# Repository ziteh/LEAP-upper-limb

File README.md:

# LEAP Upper Limb

> **Note**
> This study has ended and is no longer updated.

***LEAP-Up***, or "Lightweight Exoskeleton with Assistive Power, Upper Limb" is an upper limb powered exoskeleton based on the experience of develop [LEAP](https://github.com/ziteh/LEAP).  

- Firmware
  - [Master controller](/stm32/hi-level/): STM32Cube, STM32 HAL
  - [SIE joint code](/stm32/stm32_simple_foc/): PlatformIO, simpleFOC
  - [SFE joint code](/stm32/stm32_simple_foc/): PlatformIO, simopleFOC
  - [EFE joint code](/stm32/maxon_escon_pid_control/): PlatformIO, LibOpenCM3
- Hardware
  - PCB
    - [Master controller](/pcb/master-controller/)
    - [SIE/SFE joint](/pcb/motor-controller_simpleFOC/)
    - [EFE joint](/pcb/motor-controller_maxon/)
  - [Mechanical](/3d_model/)

# Part List

- MCU
  - STM32 NUCLEO-F446RE: Master controller and EFE joint
  - STM32 NUCLEO-L432KC: SIE and SFE joints
- Gear
  - SHD-25-100-2SH-SP: SIE joint
  - CSD-32-100-2A-GR: SFE joint
  - maxon GP 32 S: EFE joint
- Motor
  - T-Motor U8: SIE joint
  - T-Motor U10II: SFE joint
  - maxon EC-i30: EFE joint
- Motor Driver
  - ZONRI DRV8302: SIE and SFE joints
  - maxon ESCON 70/10: EFE joint
- Sensor
  - WACOH WEF-6A200-4-RCD: 6-Axis force sensor
  - ams-OSRAM AS5047P: Angle sensor/encoder
- Others
  - MAX490: RS-422 to UART

# Environment

- Ubuntu 20.04.3 'Focal Fossa' LTS (64-bit)
  - ROS 2 Foxy Fitzroy
- MATLAB R2020a
  - Robotics Toolbox for MATLAB `Ver. 10.4`
- STM32
  - PlatformIO IDE for VSCode `Ver. 3.4.4`
    - Core `Ver. 6.1.9`
    - Platform: ST STM32 `Ver. 15.6.0`
  - ~~Atollic TrueSTUDIO for STM32 `Ver. 9.3.0`~~
  - STM32Cube
    - MX: `Ver 6.7.0`
    - IDE: `Ver 1.12.0`
  - SimpleFOC: `Ver 2.2.3`
- Autodesk Inventor professional 2022

# Reference

- [SimpleFOC](https://simplefoc.com/)
- [stm32-examples](https://github.com/ziteh/stm32-examples)
  - [libopencm3](https://ziteh.github.io/series/%E7%B0%A1%E5%96%AE%E5%85%A5%E9%96%80-libopencm3-stm32-%E5%B5%8C%E5%85%A5%E5%BC%8F%E7%B3%BB%E7%B5%B1%E9%96%8B%E7%99%BC/)
- [libopencm3 Developer Documentation](https://libopencm3.org/docs/latest/html/index.html)

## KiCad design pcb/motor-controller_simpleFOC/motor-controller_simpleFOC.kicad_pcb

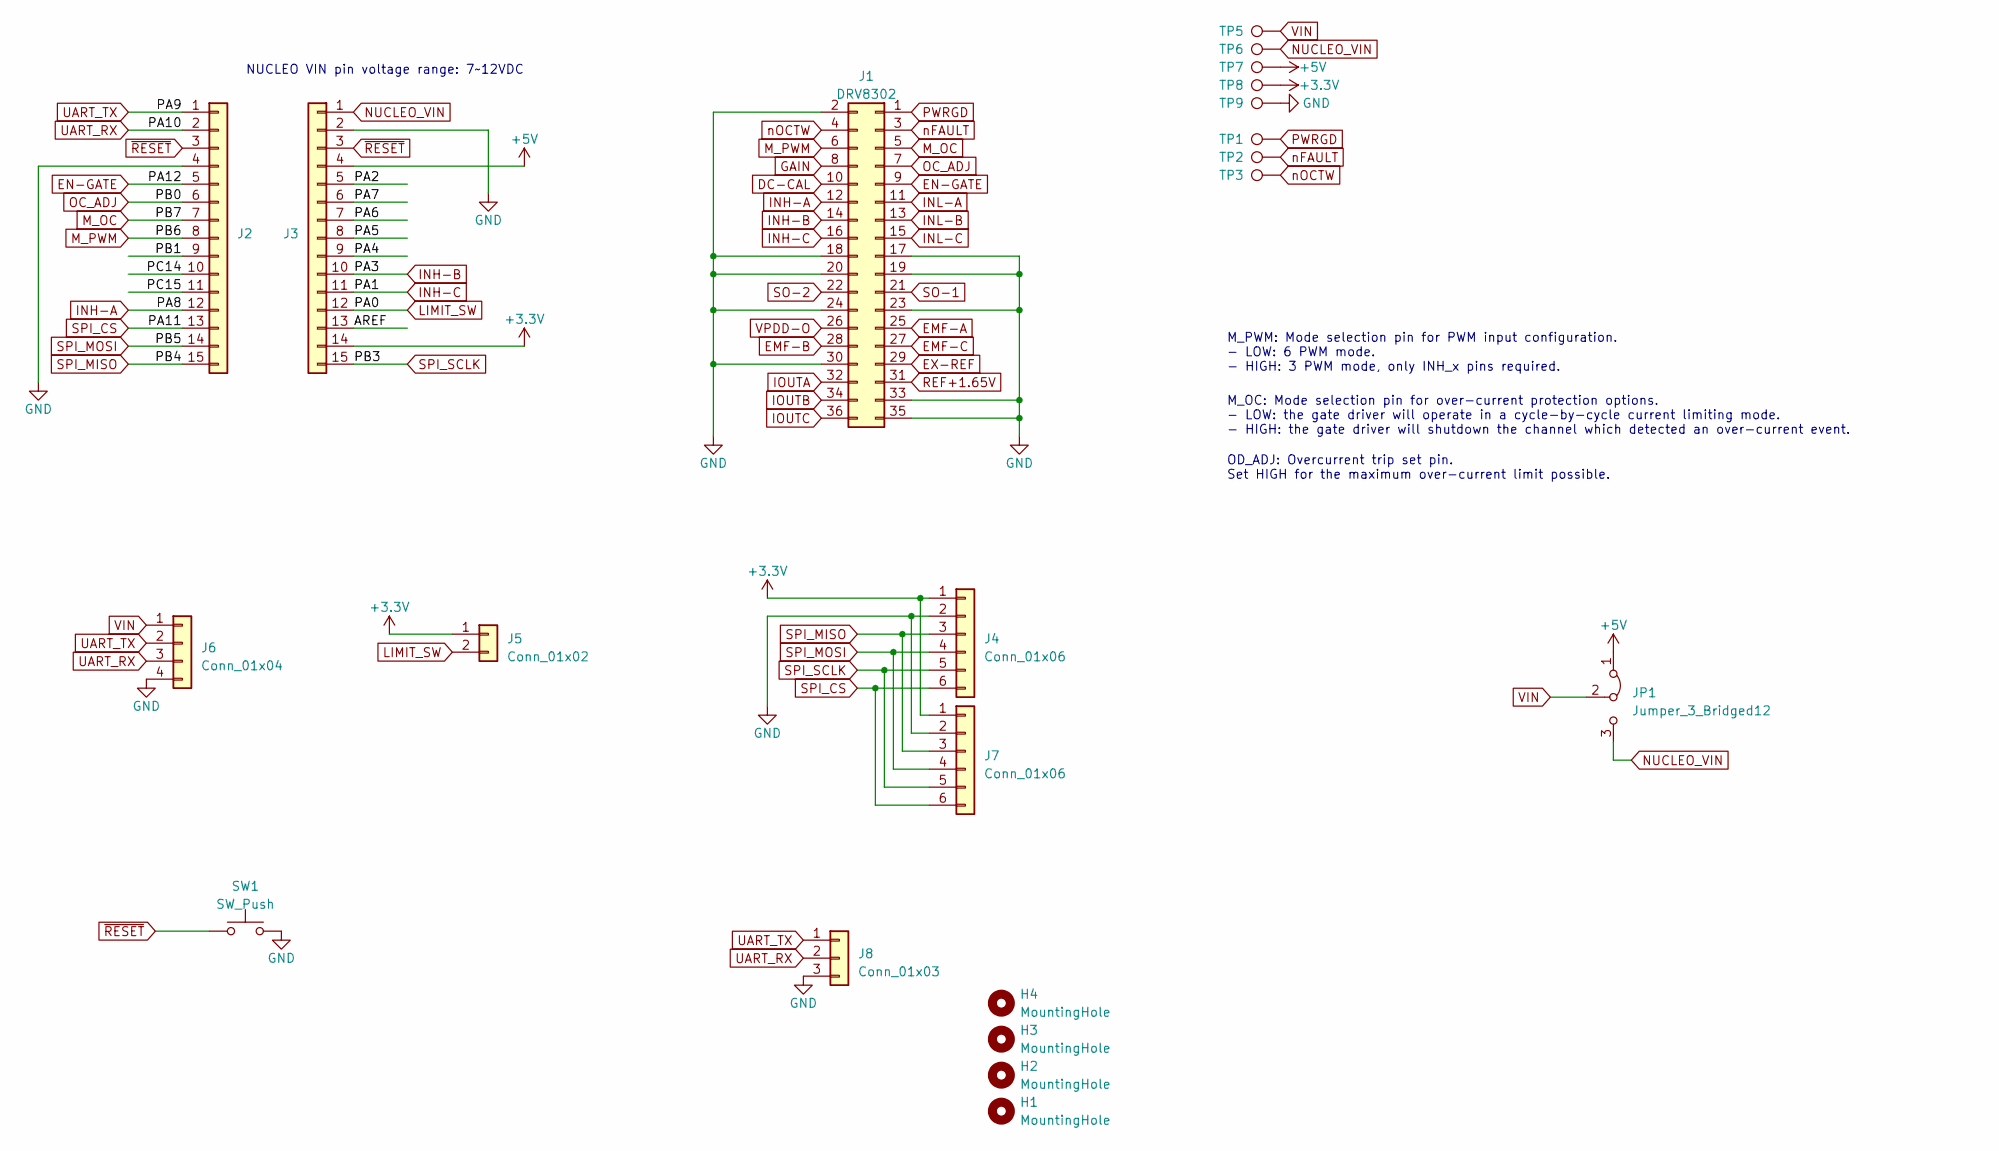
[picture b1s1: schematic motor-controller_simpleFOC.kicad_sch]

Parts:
H1, H2, H3, H4: MountingHole; MountingHole_3.5mm
J1: DRV8302; PinHeader_2x18_P2.54mm_Vertical
J2, J3: Conn_01x15; PinHeader_1x15_P2.54mm_Vertical
J4: Conn_01x06; PinHeader_1x06_P2.54mm_Vertical
J5: Conn_01x02; PinHeader_1x02_P2.54mm_Vertical
J6: Conn_01x04; JST_XH_S4B-XH-A_1x04_P2.50mm_Horizontal
J7: Conn_01x06; JST_XH_S6B-XH-A_1x06_P2.50mm_Horizontal
J8: Conn_01x03; PinHeader_1x03_P2.54mm_Vertical
JP1: Jumper_3_Bridged12; PinHeader_1x03_P2.54mm_Vertical
SW1: SW_Push; SW_SPST_CK_RS282G05A3
TP1, TP2, TP3, TP5, TP6, TP7, TP8, TP9: TestPoint; TestPoint_Pad_D1.5mm

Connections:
+3.3V: J3.14, J4.1, J5.1, J7.1, TP8.1
+5V: J3.4, JP1.1 (A), TP7.1
/AREF: J3.13
/PA2: J3.5
/PA4: J3.9
/PA5: J3.8
/PA6: J3.7
/PA7: J3.6
/PB1: J2.9
/PC14: J2.10
/PC15: J2.11
DC-CAL: J1.10
EMF-A: J1.25
EMF-B: J1.28
EMF-C: J1.27
EN-GATE: J1.9, J2.5
EX-REF: J1.29
GAIN: J1.8
GND: J1.2, J1.17, J1.18, J1.19, J1.20, J1.23, J1.24, J1.30, J1.33, J1.35, J2.4, J3.2, J4.2, J6.4, J7.2, J8.3, SW1.2, TP9.1
INH-A: J1.12, J2.12
INH-B: J1.14, J3.10
INH-C: J1.16, J3.11
INL-A: J1.11
INL-B: J1.13
INL-C: J1.15
IOUTA: J1.32
IOUTB: J1.34
IOUTC: J1.36
LIMIT_SW: J3.12, J5.2
M_OC: J1.5, J2.7
M_PWM: J1.6, J2.8
NUCLEO_VIN: J3.1, JP1.3 (B), TP6.1
OC_ADJ: J1.7, J2.6
PWRGD: J1.1, TP1.1
REF+1.65V: J1.31
SO-1: J1.21
SO-2: J1.22
SPI_CS: J2.13, J4.6, J7.6
SPI_MISO: J2.15, J4.3, J7.3
SPI_MOSI: J2.14, J4.4, J7.4
SPI_SCLK: J3.15, J4.5, J7.5
UART_RX: J2.2, J6.3, J8.2
UART_TX: J2.1, J6.2, J8.1
VIN: J6.1, JP1.2 (C), TP5.1
VPDD-O: J1.26
nFAULT: J1.3, TP2.1
nOCTW: J1.4, TP3.1
~RESET: J2.3, J3.3, SW1.1

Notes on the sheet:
M_OC: Mode selection pin for over-current protection options. - LOW: the gate driver will operate in a cycle-by-cycle current limiting mode. - HIGH: the gate driver will shutdown the channel which detected an over-current event.
NUCLEO VIN pin voltage range: 7~12VDC
OD_ADJ: Overcurrent trip set pin. Set HIGH for the maximum over-current limit possible.
M_PWM: Mode selection pin for PWM input configuration. - LOW: 6 PWM mode. - HIGH: 3 PWM mode, only INH_x pins required.

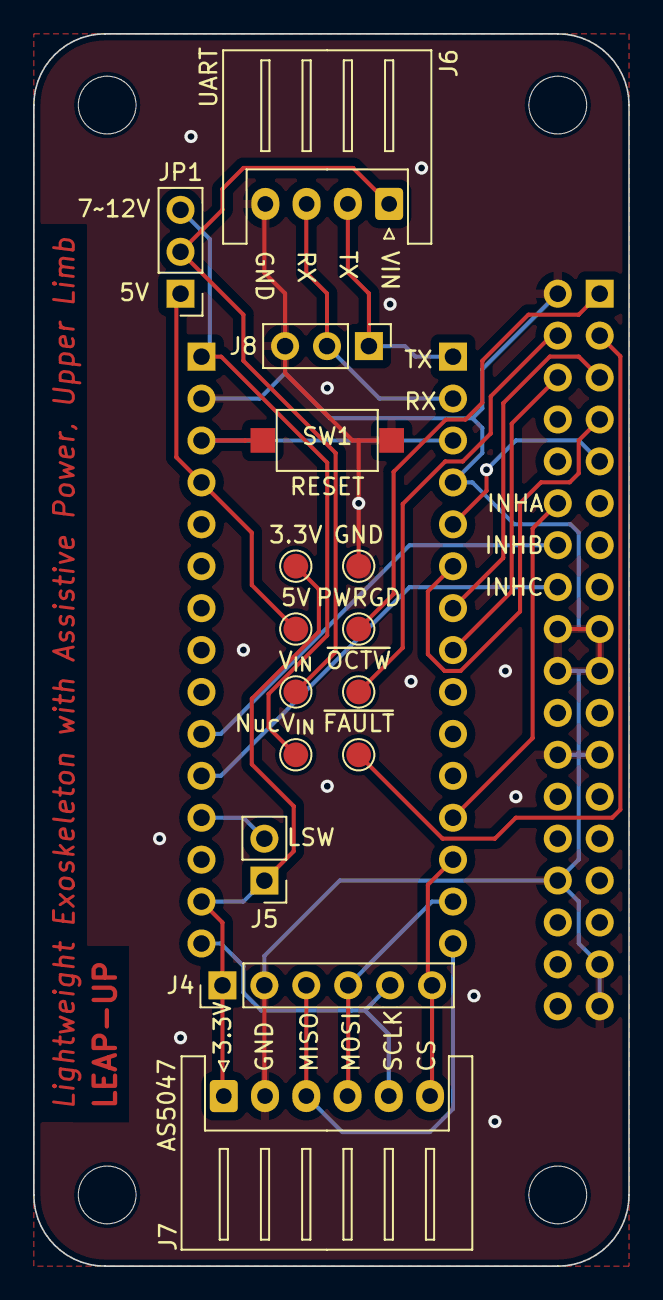
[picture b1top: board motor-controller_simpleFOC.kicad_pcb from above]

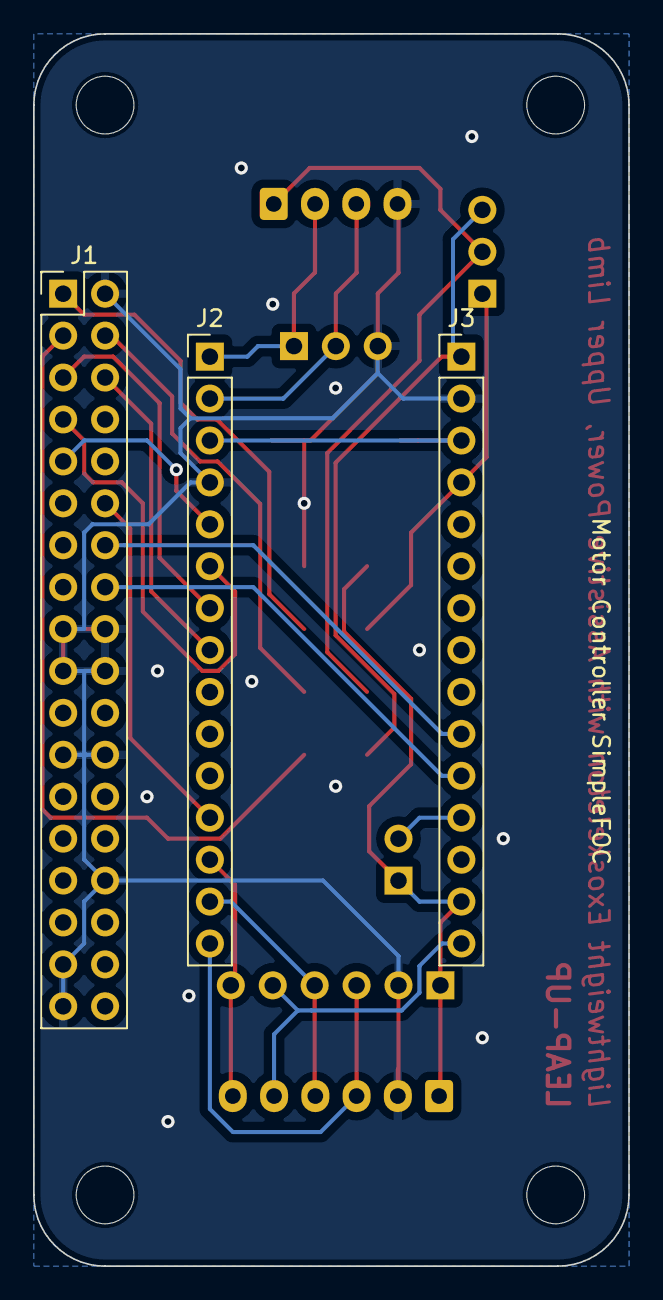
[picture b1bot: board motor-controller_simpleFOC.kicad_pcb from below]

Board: 2 copper layers, 36.1 x 74.7 mm, 22 parts (3 on the bottom side), 23 nets.

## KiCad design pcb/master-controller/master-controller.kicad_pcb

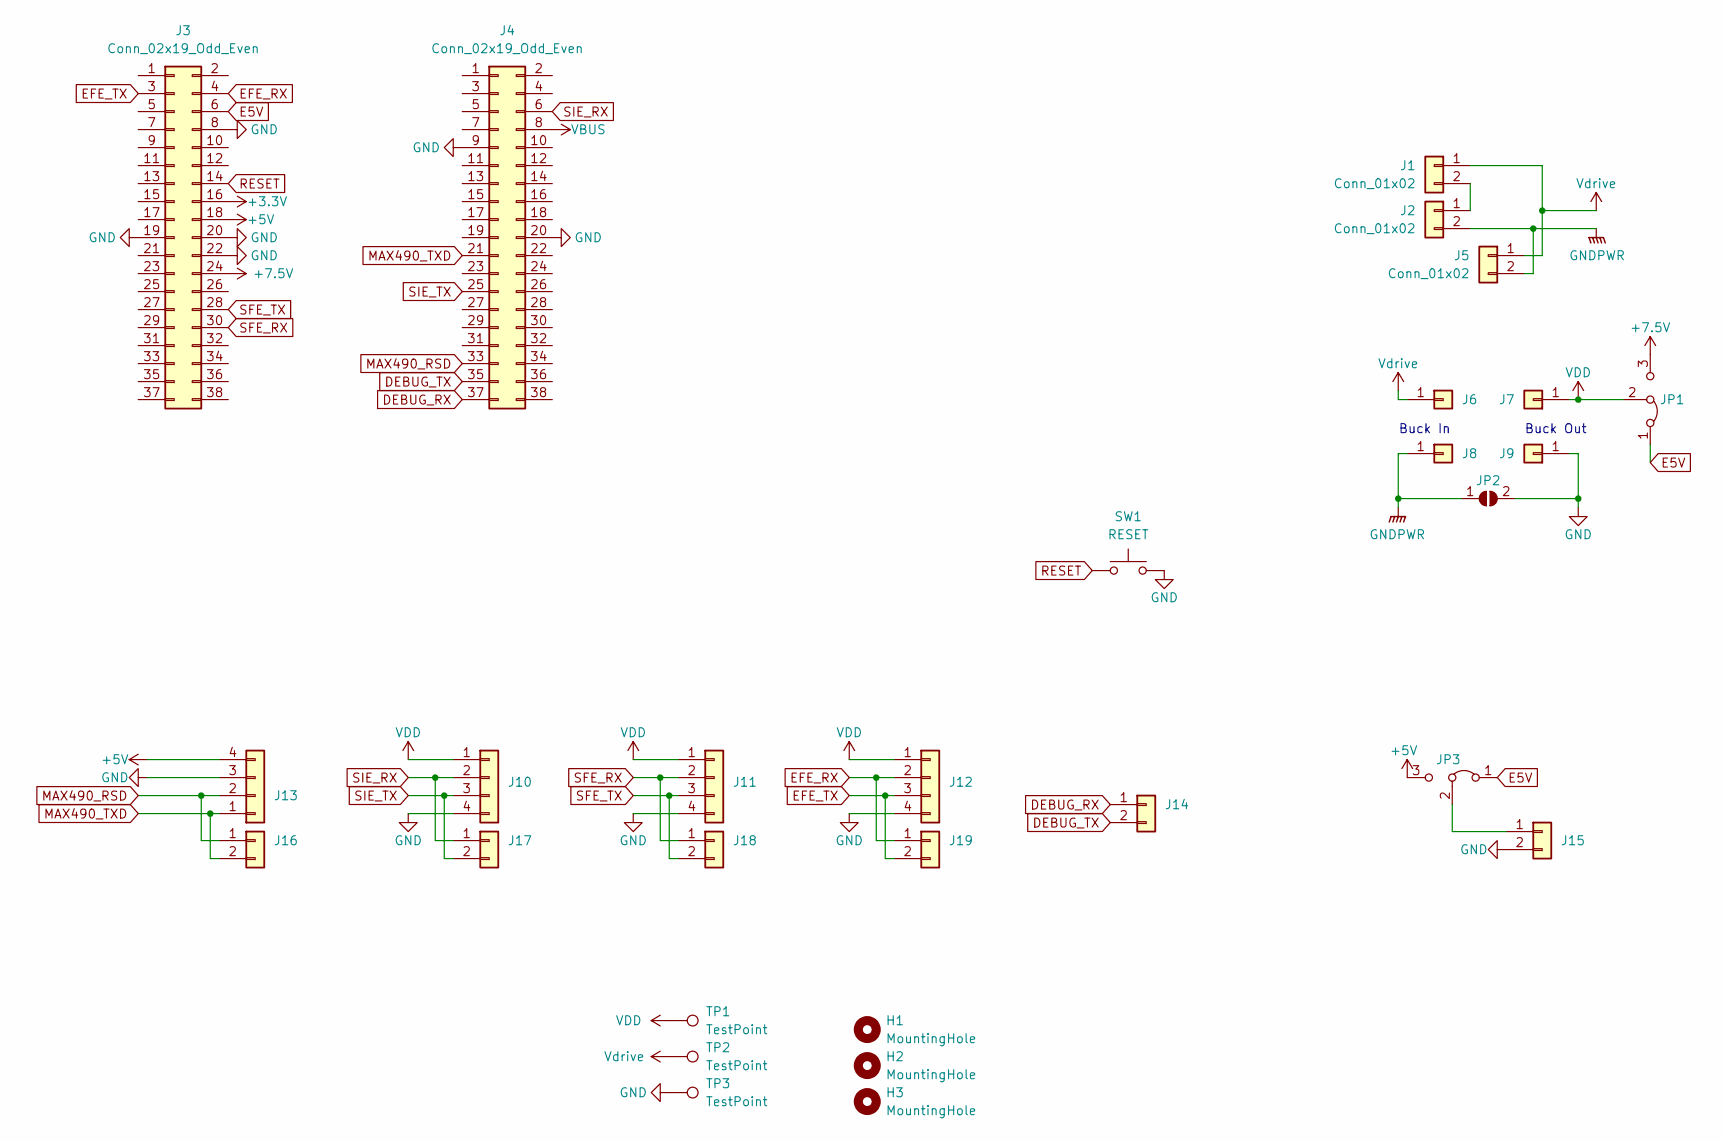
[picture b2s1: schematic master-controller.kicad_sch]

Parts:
H1, H2, H3: MountingHole; MountingHole_3.5mm
J1, J2: Conn_01x02; AMASS_XT60-M_1x02_P7.20mm_Vertical
J3, J4: Conn_02x19_Odd_Even; PinSocket_2x19_P2.54mm_Vertical
J5, J14, J16, J17, J18, J19: Conn_01x02; PinHeader_1x02_P2.54mm_Vertical
J6, J7, J8, J9: Conn_01x01; PinHeader_1x01_P2.54mm_Vertical
J10, J11, J12, J13: Conn_01x04; JST_XH_B4B-XH-A_1x04_P2.50mm_Vertical
J15: FT_sensor_power; PinHeader_1x02_P2.54mm_Vertical
JP1, JP3: Jumper_3_Bridged12; PinHeader_1x03_P2.54mm_Vertical
JP2: SolderJumper_2_Open; SolderJumper-2_P1.3mm_Open_RoundedPad1.0x1.5mm
SW1: RESET; SW_SPST_CK_RS282G05A3
TP1, TP2, TP3: TestPoint; TestPoint_Pad_D1.5mm

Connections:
+3.3V: J3.16
+5V: J3.18, J13.4, JP3.3 (B)
+7.5V: J3.24, JP1.3 (B)
DEBUG_RX: J4.37, J14.1
DEBUG_TX: J4.35, J14.2
E5V: J3.6, JP1.1 (A), JP3.1 (A)
EFE_RX: J3.4, J12.2, J19.1
EFE_TX: J3.3, J12.3, J19.2
GND: J3.8, J3.19, J3.20, J3.22, J4.9, J4.20, J9.1, J10.4, J11.4, J12.4, J13.3, J15.2, JP2.2 (B), SW1.2, TP3.1
GNDPWR: J2.2, J5.2, J8.1, JP2.1 (A)
MAX490_RSD: J4.33, J13.2, J16.1
MAX490_TXD: J4.21, J13.1, J16.2
unnamed: J1.2, J2.1
unnamed: J15.1, JP3.2 (C)
RESET: J3.14, SW1.1
SFE_RX: J3.30, J11.2, J18.1
SFE_TX: J3.28, J11.3, J18.2
SIE_RX: J4.6, J10.2, J17.1
SIE_TX: J4.25, J10.3, J17.2
VBUS: J4.8
VDD: J7.1, J10.1, J11.1, J12.1, JP1.2 (C), TP1.1
Vdrive: J1.1, J5.1, J6.1, TP2.1

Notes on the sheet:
Buck In
Buck Out

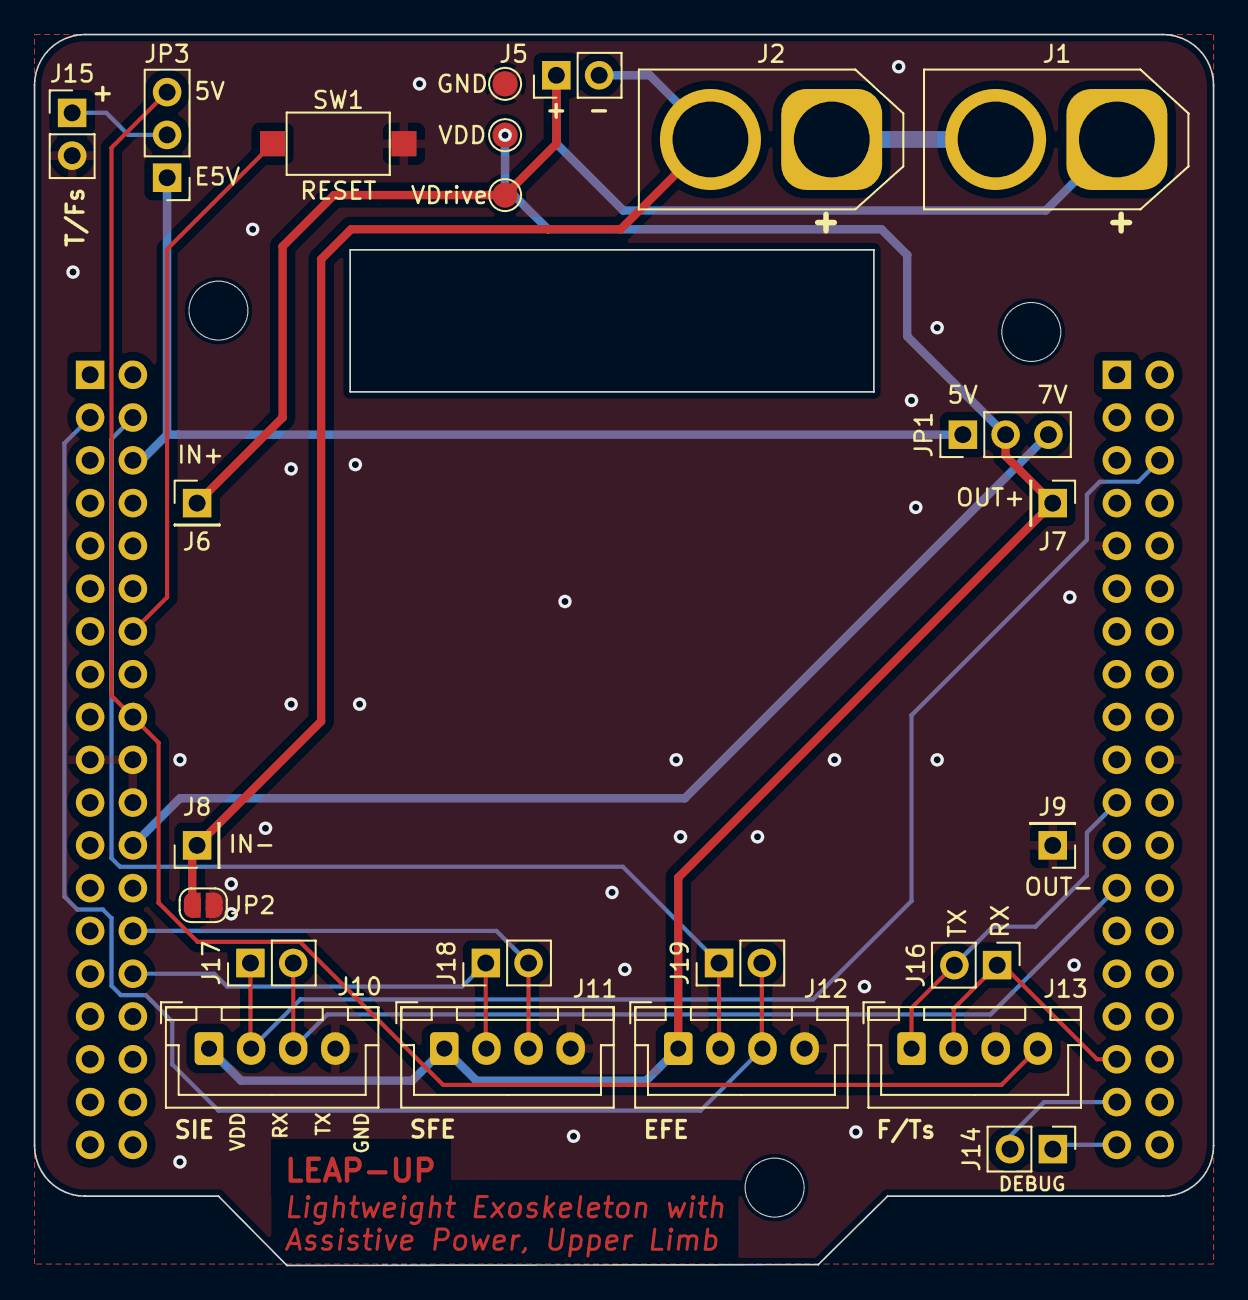
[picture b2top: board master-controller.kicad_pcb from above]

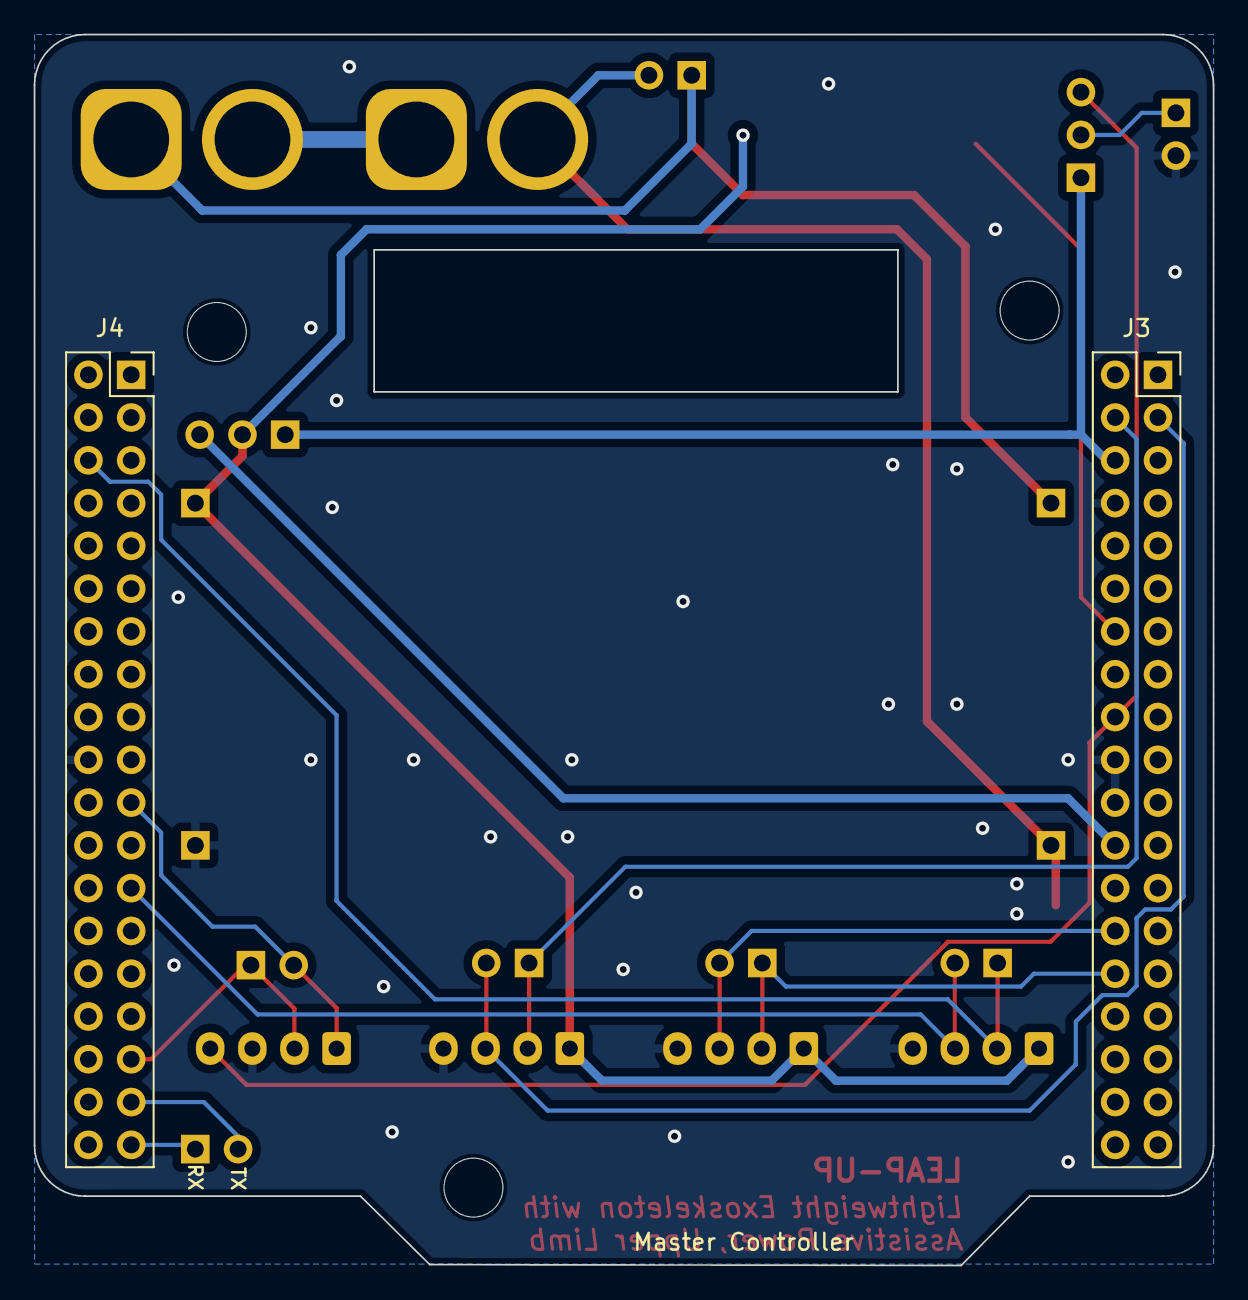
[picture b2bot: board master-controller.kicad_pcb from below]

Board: 2 copper layers, 70.0 x 73.1 mm, 29 parts (2 on the bottom side), 20 nets.

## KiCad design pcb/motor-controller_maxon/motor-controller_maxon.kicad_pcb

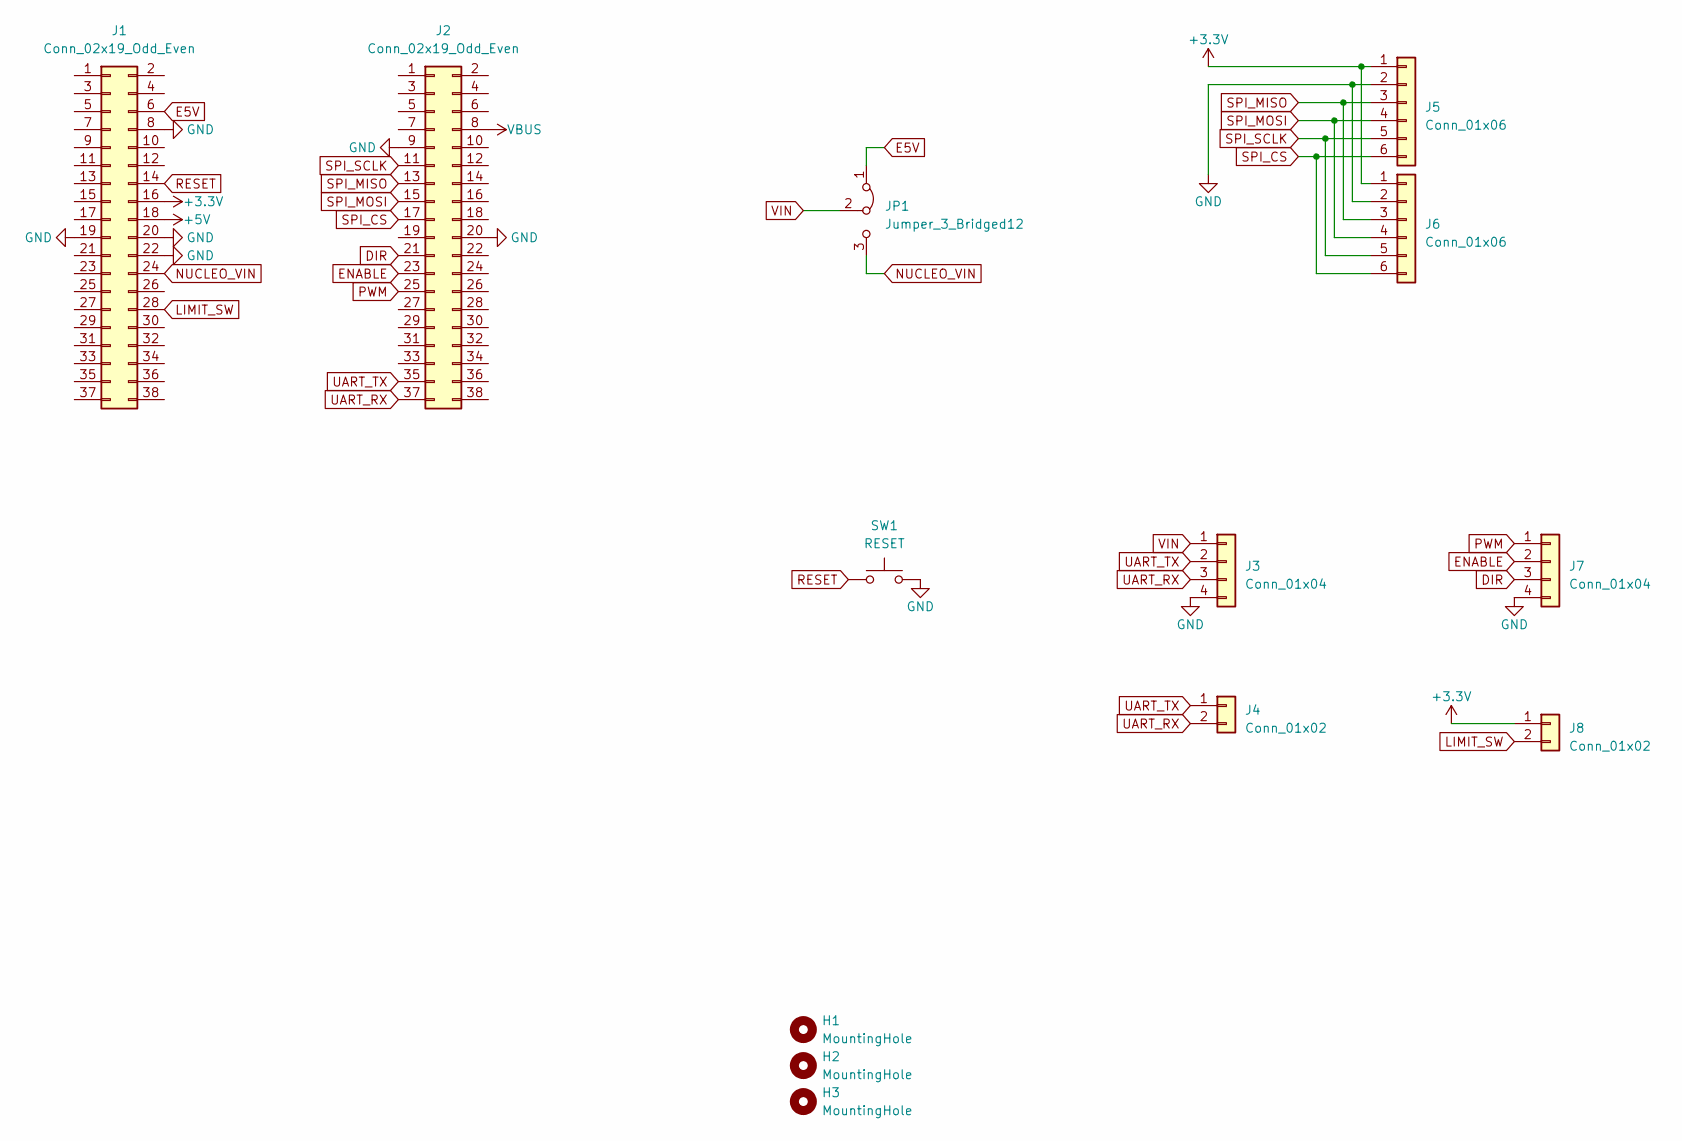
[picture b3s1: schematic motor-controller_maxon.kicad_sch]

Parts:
H1, H2, H3: MountingHole; MountingHole_3.5mm
J1, J2: Conn_02x19_Odd_Even; PinSocket_2x19_P2.54mm_Vertical
J3, J7: Conn_01x04; JST_XH_S4B-XH-A_1x04_P2.50mm_Horizontal
J4, J8: Conn_01x02; PinHeader_1x02_P2.54mm_Vertical
J5: Conn_01x06; PinHeader_1x06_P2.54mm_Vertical
J6: Conn_01x06; JST_XH_S6B-XH-A_1x06_P2.50mm_Horizontal
JP1: Jumper_3_Bridged12; PinHeader_1x03_P2.54mm_Vertical
SW1: RESET; SW_SPST_CK_RS282G05A3

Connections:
+3.3V: J1.16, J5.1, J6.1, J8.1
+5V: J1.18
DIR: J2.21, J7.3
E5V: J1.6, JP1.1 (A)
ENABLE: J2.23, J7.2
GND: J1.8, J1.19, J1.20, J1.22, J2.9, J2.20, J3.4, J5.2, J6.2, J7.4, SW1.2
LIMIT_SW: J1.28, J8.2
NUCLEO_VIN: J1.24, JP1.3 (B)
PWM: J2.25, J7.1
RESET: J1.14, SW1.1
SPI_CS: J2.17, J5.6, J6.6
SPI_MISO: J2.13, J5.3, J6.3
SPI_MOSI: J2.15, J5.4, J6.4
SPI_SCLK: J2.11, J5.5, J6.5
UART_RX: J2.37, J3.3, J4.2
UART_TX: J2.35, J3.2, J4.1
VBUS: J2.8
VIN: J3.1, JP1.2 (C)

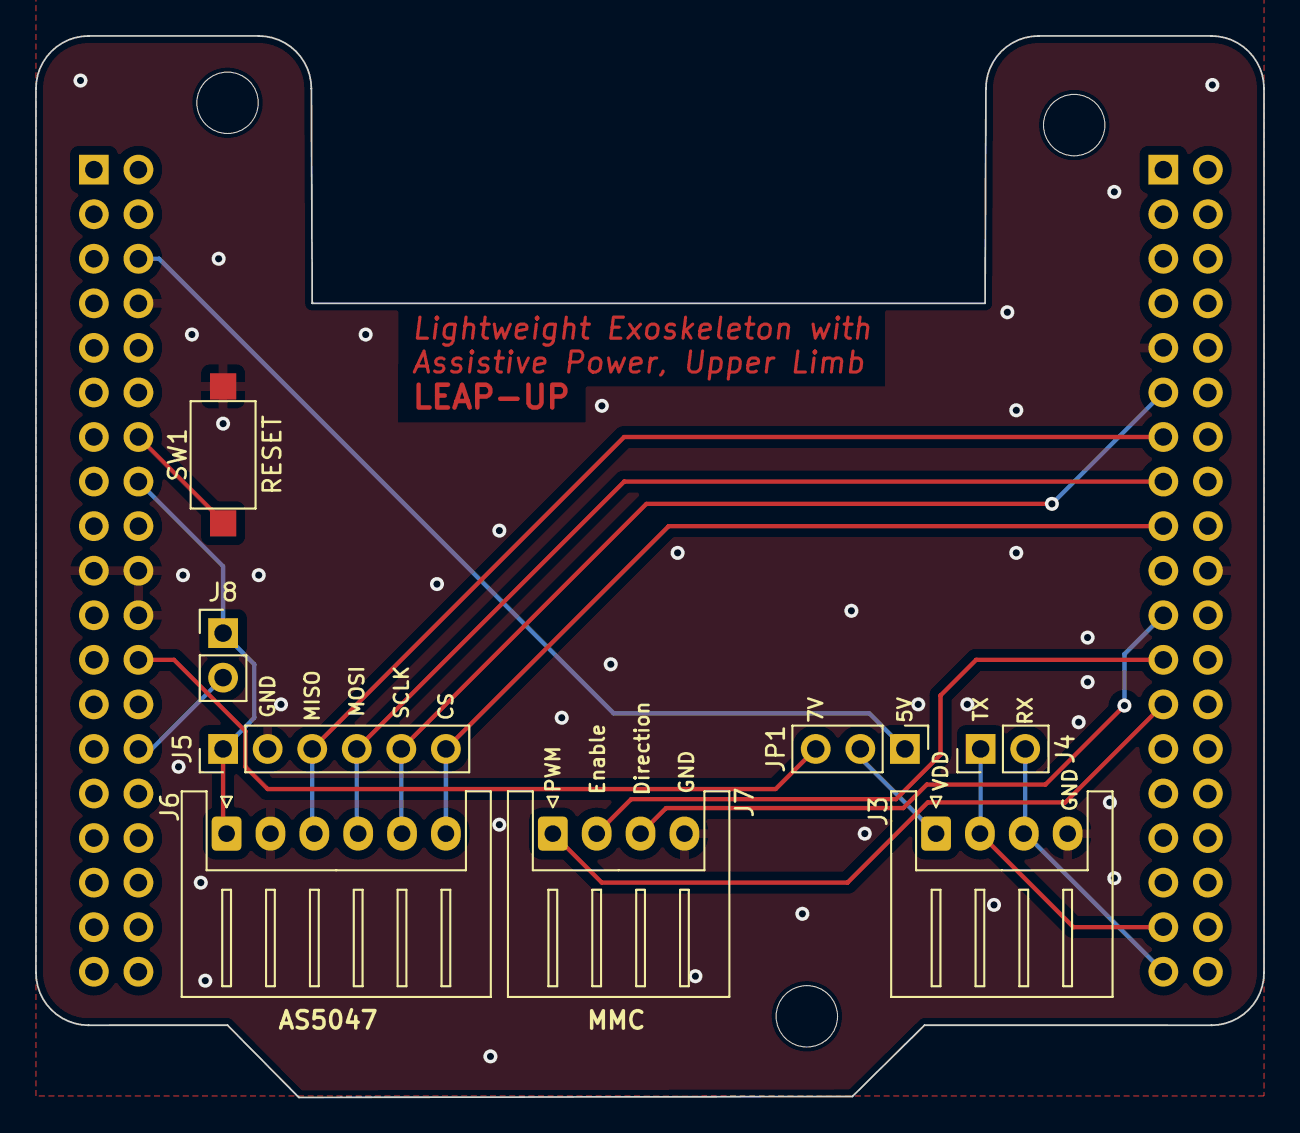
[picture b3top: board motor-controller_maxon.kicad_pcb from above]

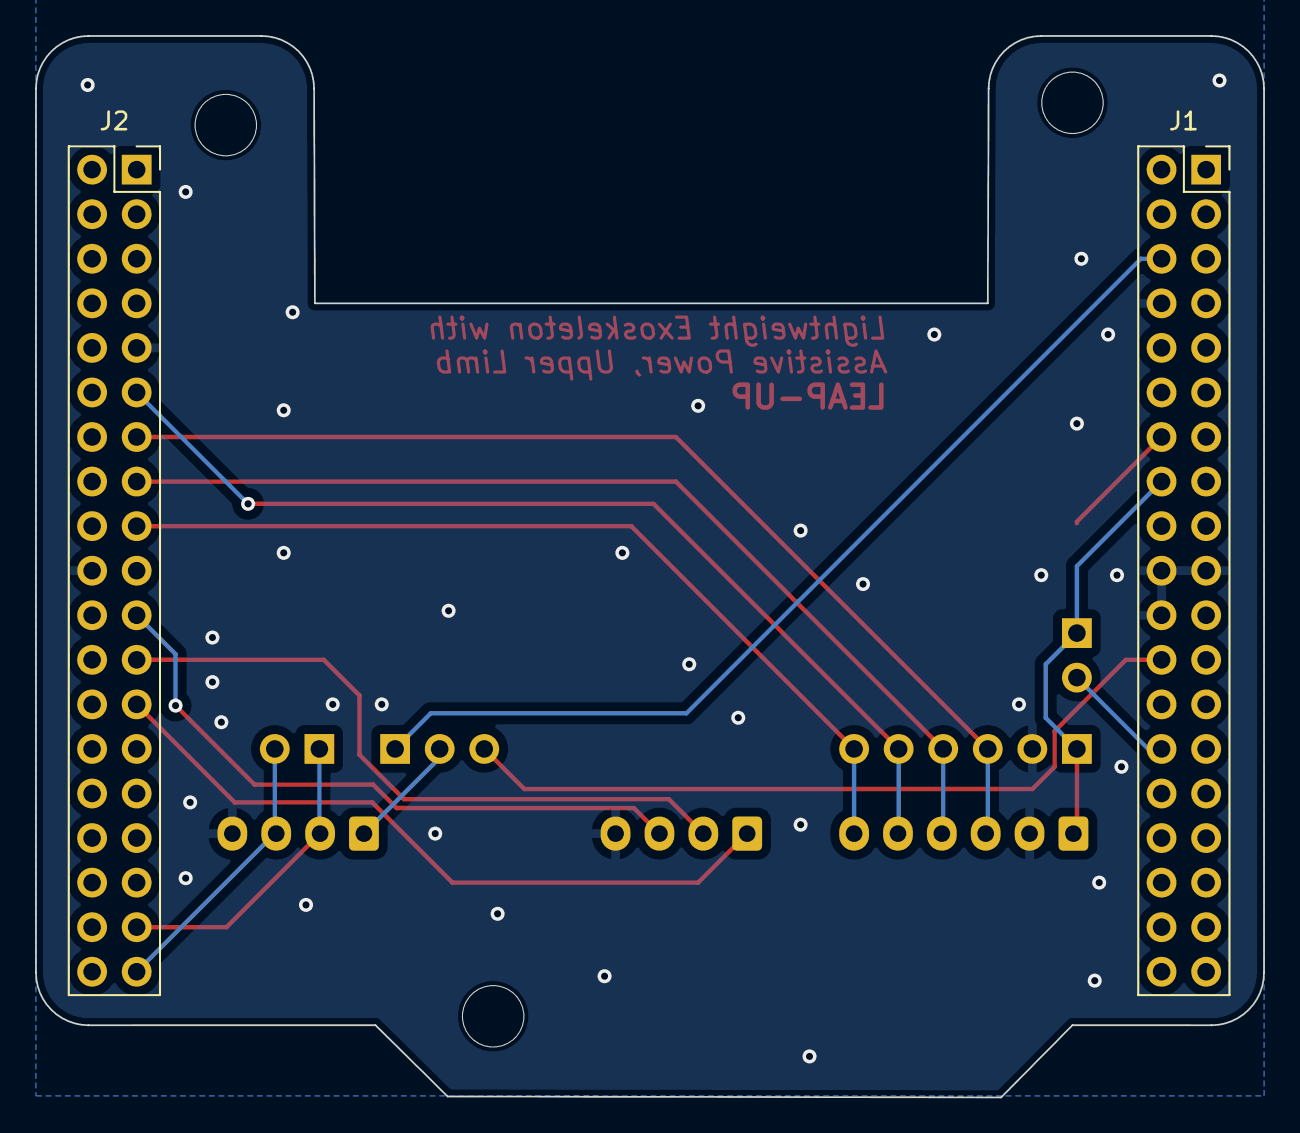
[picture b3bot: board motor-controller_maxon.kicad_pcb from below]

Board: 2 copper layers, 70.0 x 60.5 mm, 13 parts (2 on the bottom side), 16 nets.

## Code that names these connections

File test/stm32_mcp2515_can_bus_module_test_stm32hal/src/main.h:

#include <stm32f3xx_hal.h>
#include "mcp2515.h"

#define UART_BAUDRATE (9600)

#define GPIO_UART_TX_PORT (GPIOA)
#define GPIO_UART_TX_PIN (GPIO_PIN_2)

#define GPIO_UART_RX_PORT (GPIOA)
#define GPIO_UART_RX_PIN (GPIO_PIN_3)

#define GPIO_LED_PORT (GPIOB)
#define GPIO_LED_PIN (GPIO_PIN_13)

#define GPIO_SPI_SCK_PORT (GPIOB)
#define GPIO_SPI_SCK_PIN (GPIO_PIN_13)

#define GPIO_SPI_MISO_PORT (GPIOB)
#define GPIO_SPI_MISO_PIN (GPIO_PIN_14)

#define GPIO_SPI_MOSI_PORT (GPIOB)
#define GPIO_SPI_MOSI_PIN (GPIO_PIN_15)

#define GPIO_SPI_CS_PORT (GPIOB)
#define GPIO_SPI_CS_PIN (GPIO_PIN_6)

void SPI_SELECT();
void SPI_DESELECT();
void spi_start(void);
void spi_end(void);

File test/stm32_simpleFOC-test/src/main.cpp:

/**
 * @file main.cpp
 * @brief STM32 SimpleFOC basic test.
 */

#include <Arduino.h>
#include <SimpleFOC.h>

// DRV8302 pins connections
// don't forget to connect the common ground pin
#define INH_A (9)
#define INH_B (10)
#define INH_C (11)

#define EN_GATE (8)
#define M_PWM (6)
#define M_OC (5)
#define OC_ADJ (7)

#define VOLTAGE (24)

// motor instance
BLDCMotor motor = BLDCMotor(21, 0.137); // T-Motor U8
// BLDCMotor motor = BLDCMotor(11, 0.216); // Maxon EC90flat
// BLDCMotor motor = BLDCMotor(7, 0.090); // A2212/6T 2200KV

// driver instance
BLDCDriver3PWM driver = BLDCDriver3PWM(INH_A, INH_B, INH_C, EN_GATE);

// encoder instance
// Encoder encoder = Encoder(2, 3, 4000);
// channel A and B callbacks
// void doA() { encoder.handleA(); }
// void doB() { encoder.handleB(); }
// void doIndex() { encoder.handleIndex(); }

// InlineCurrentSensor constructor
//  - shunt_resistor  - shunt resistor value
//  - gain  - current-sense op-amp gain
//  - phA   - A phase adc pin
//  - phB   - B phase adc pin
//  - phC   - C phase adc pin (optional)
// InlineCurrentSense current_sense = InlineCurrentSense(0.005, 12.22, A0, A1, A2);

// Hall sensor instance
// HallSensor(int hallA, int hallB , int cpr, int index)
//  - hallA, hallB, hallC    - HallSensor A, B and C pins
//  - pp                     - pole pairs
// HallSensor sensor = HallSensor(A2, A1, A0, 11);
// Interrupt routine initialization
// channel A and B callbacks
// void doA() { sensor.handleA(); }
// void doB() { sensor.handleB(); }
// void doC() { sensor.handleC(); }

// commander interface
Commander command = Commander(Serial);
void onMotor(char *cmd) { command.motor(&motor, cmd); }

void setup()
{
  // initialize encoder sensor hardware
  // encoder.init();
  // encoder.enableInterrupts(doA, doB, doIndex);
  // encoder.enableInterrupts(doA, doB);

  // check if you need internal pullups
  // Pullup::USE_EXTERN - external pullup added  - default
  // Pullup::USE_INTERN - needs internal arduino pullup
  // encoder.pullup = Pullup::USE_INTERN;

  // link the motor to the sensor
  // motor.linkSensor(&encoder);

  // current sense
  // current_sense.init();
  // motor.linkCurrentSense(&current_sense);
  // sensor.pullup = Pullup::USE_INTERN;
  // sensor.init();
  // hardware interrupt enable
  // sensor.enableInterrupts(doA, doB, doC);
  // motor.linkSensor(&sensor);

  // DRV8302 specific code
  // M_OC  - enable over-current protection
  pinMode(M_OC, OUTPUT);
  digitalWrite(M_OC, LOW);
  // M_PWM  - enable 3pwm mode
  pinMode(M_PWM, OUTPUT);
  digitalWrite(M_PWM, HIGH);
  // OD_ADJ - set the maximum over-current limit possible
  // Better option would be to use voltage divisor to set exact value
  pinMode(OC_ADJ, OUTPUT);
  digitalWrite(OC_ADJ, HIGH);

  // configure driver
  driver.voltage_power_supply = VOLTAGE;
  driver.init();
  motor.linkDriver(&driver);

  // choose FOC modulation
  motor.foc_modulation = FOCModulationType::SpaceVectorPWM;

  // motor.torque_controller = TorqueControlType::voltage;

  // set control loop type to be used
  // motor.controller = MotionControlType::torque;
  motor.controller = MotionControlType::angle_openloop;
  // motor.controller = MotionControlType::velocity_openloop;

  // controller configuration based on the control type
  motor.PID_velocity.P = 0.2;
  motor.PID_velocity.I = 20;
  // motor.PID_velocity.D = 0.005;

  motor.PID_velocity.output_ramp = 50;

  // velocity low pass filtering time constant
  motor.LPF_velocity.Tf = 0.01;

  // angle loop controller
  motor.P_angle.P = 0.1;
  // motor.P_angle.D = 0.02;
  motor.P_angle.output_ramp = 1;

  // angle loop velocity limit
  motor.velocity_limit = 12;
  // default voltage_power_supply
  motor.voltage_limit = VOLTAGE;
  motor.current_limit = 6.5;

  // use monitoring with serial for motor init
  // monitoring port
  Serial.begin(115200);
  // comment out if not needed
  motor.useMonitoring(Serial);

  // initialize motor
  motor.init();
  // align encoder and start FOC
  motor.initFOC();

  // set the initial target value
  motor.target = 0;

  // define the motor id
  command.add('M', onMotor, "motor");

  _delay(1000);
}

void loop()
{
  // iterative setting FOC phase voltage
  motor.loopFOC();

  // iterative function setting the outer loop target
  // velocity, position or voltage
  // if target not set in parameter uses motor.target variable
  motor.move();

  // motor.monitor();

  // user communication
  command.run();

  // sensor.update();
  // Serial.println(sensor.getVelocity());
}
